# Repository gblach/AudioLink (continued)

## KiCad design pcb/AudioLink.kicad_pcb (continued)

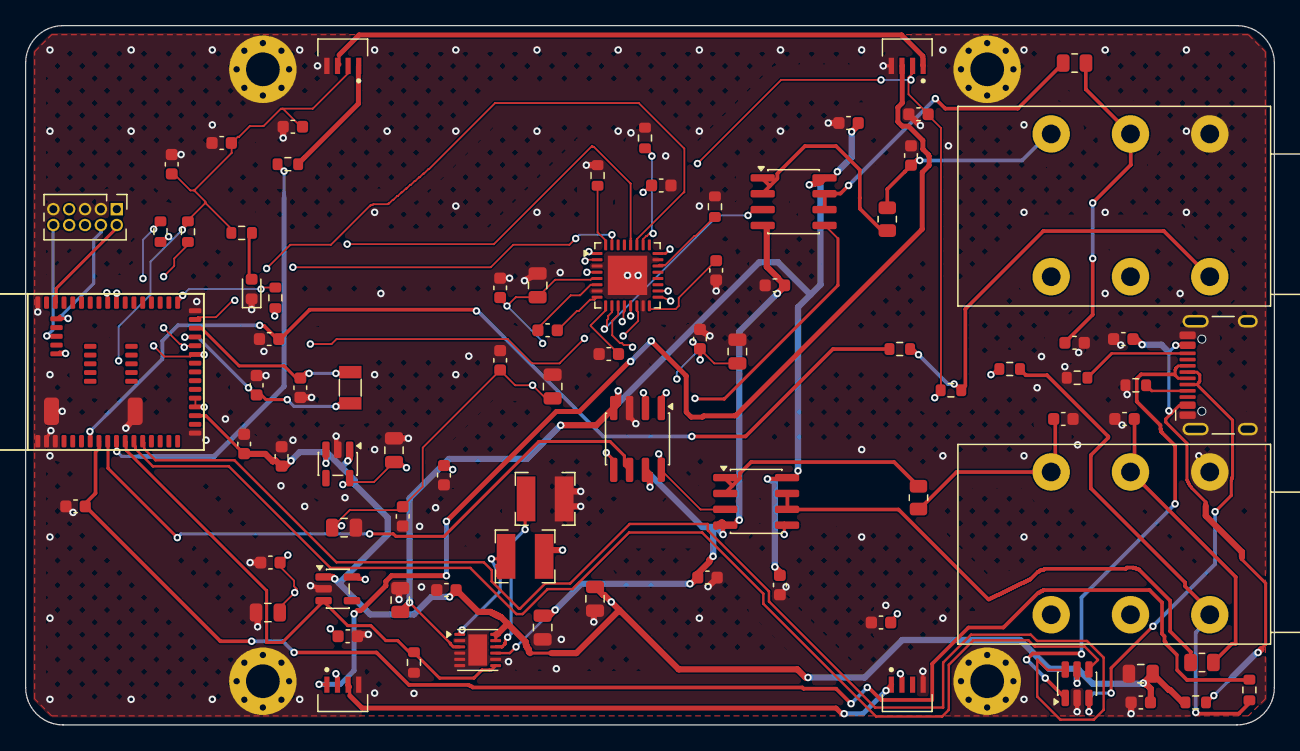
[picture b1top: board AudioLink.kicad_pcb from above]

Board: 4 copper layers, 100.0 x 56.0 mm, 88 parts (0 on the bottom side), 60 nets.

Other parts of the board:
H1, H2, H3, H4: MountingHole_2.7mm_M2.5_Pad_Via_0p5

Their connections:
GND: H1.1, H2.1, H3.1, H4.1; also elsewhere on the board

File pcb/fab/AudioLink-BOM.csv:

"Item","Designator","Qty","Manufacturer","MPN","Value","Footprint","Type","Notes"
"1","C1","1","","","4u7/10V/X7R","C_0805","SMD","LCSC: https://www.lcsc.com/search?q=4.7uF+0805+10V+X7R"
"2","C2,C6,C9,C11,C18-C20,C22,C24,C34-C43","19","","","100n/25V/X7R","C_0603","SMD","LCSC: https://www.lcsc.com/search?q=100nF+0603+25V+X7R"
"3","C3","1","","","10n/50V/X7R","C_0603","SMD","LCSC: https://www.lcsc.com/search?q=10nF+0603+50V+X7R"
"4","C4,C7,C17,C26,C29","5","","","1u/16V/X7R","C_0603","SMD","LCSC: https://www.lcsc.com/search?q=1uF+0603+16V+X7R"
"5","C5,C8,C21,C23,C25","5","","","10u/10V/X7R","C_0805","SMD","LCSC: https://www.lcsc.com/search?q=10uF+0805+10V+X7R"
"6","C10","1","","","22u/10V/X7R","C_0805","SMD","LCSC: https://www.lcsc.com/search?q=22uF+0805+10V+X7R"
"7","C12-C14","3","","","10u/16V/X7R","C_0805","SMD","LCSC: https://www.lcsc.com/search?q=10uF+0805+16V+X7R"
"8","C15,C16","2","","","7p/50V/C0G","C_0603","SMD","LCSC: https://www.lcsc.com/search?q=7pF+0603+50V+C0G. C0G required - crystal load capacitor"
"9","C27,C28","2","","","2u2/16V/X7R","C_0603","SMD","LCSC: https://www.lcsc.com/search?q=2.2uF+0603+16V+X7R"
"10","C30-C33","4","","","100p/50V/C0G","C_0603","SMD","LCSC: https://www.lcsc.com/search?q=100pF+0603+50V+C0G. C0G required - audio output EMI shunt"
"11","D1-D4","4","Worldsemi","WS2812B-4020-V6","WS2812B-4020-V6","LED_WS2812B-4020","SMD","LCSC C52941387 - https://www.lcsc.com/search?q=C52941387"
"12","D5","1","Gui guang light","GL0603UB01","Blue","LED_0603","SMD","LCSC C51933294 - https://www.lcsc.com/search?q=C51933294. Low-Vf blue, 2.6-2.9V - needed because R19 leaves only 0.4-0.7V across it from the 3V3 rail"
"13","D6","1","STMicroelectronics","USBLC6-2SC6","USBLC6-2SC6","SOT-23-6","SMD","LCSC C7519 - https://www.lcsc.com/search?q=C7519. Genuine ST. Cheaper UMW equivalent C2687116 - https://www.lcsc.com/search?q=C2687116"
"14","FB1","1","Murata","BLM18PG221SN1D","220R@100MHz","R_0603","SMD","LCSC C80165 - https://www.lcsc.com/search?q=C80165"
"15","L1,L2","2","Sunlord","SWPA4020S4R7MT","4u7/1.34A","L_Bourns-SRN4018","SMD","LCSC C48427 - https://www.lcsc.com/search?q=C48427"
"16","R1,R2","2","","","5k1/1%","R_0603","SMD","LCSC: https://www.lcsc.com/search?q=5.1k+0603+1%. 1% required - USB-C CC pulldown"
"17","R3,R12,R13","3","","","100k","R_0603","SMD","LCSC: https://www.lcsc.com/search?q=100k+0603"
"18","R4,R5","2","","","4k7","R_0603","SMD","LCSC: https://www.lcsc.com/search?q=4.7k+0603"
"19","R7,R17,R18","3","","","0R","R_0603","SMD","LCSC: https://www.lcsc.com/search?q=0R+0603"
"20","R8-R11","4","","","100R/1%","R_0805","SMD","LCSC: https://www.lcsc.com/search?q=100R+0805+1%. 1% required - these set the balanced source impedance and CMRR"
"21","R14,R15","2","","","10k","R_0603","SMD","LCSC: https://www.lcsc.com/search?q=10k+0603"
"22","R16,R19","2","","","470R","R_0603","SMD","LCSC: https://www.lcsc.com/search?q=470R+0603"
"23","U1","1","MinewSemi","MS45SF1-1Y40AIR","MS45SF1","MinewSemi_MS45SF1","SMD","Digikey - https://www.digikey.com/en/products/result?keywords=MS45SF1-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 Not stocked at LCSC"
"24","U2","1","Texas Instruments","PCM5242RHBR","PCM5242","VQFN-32","SMD","LCSC C471871 - https://www.lcsc.com/search?q=C471871"
"25","U3,U4","2","Texas Instruments","OPA1678IDR","OPA1678","SOIC-8","SMD","LCSC C192421 - https://www.lcsc.com/search?q=C192421"
"26","U5","1","Vishay","DG419DY-T1-E3","DG419","SOIC-8","SMD","LCSC C6581 - https://www.lcsc.com/search?q=C6581"
"27","U6","1","Texas Instruments","TPS65133DPDR","TPS65133","WSON-12","SMD","LCSC C134100 - https://www.lcsc.com/search?q=C134100"
"28","U7,U8","2","Texas Instruments","TLV75533PDBVR","TLV75533","SOT-23-5","SMD","LCSC C404027 - https://www.lcsc.com/search?q=C404027"
"29","Y1","1","Seiko Epson","FC-135 32.7680KA-A5","32.768kHz/7pF","Crystal_SMD_3215","SMD","Digikey - https://www.digikey.com/en/products/result?keywords=FC-135+3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 LCSC equivalent: Seiko SC-32S C97604, same 3215 / 7pF / 20ppm - https://www.lcsc.com/search?q=C97604"
"30","J1,J2","2","Neutrik","NRJ6HM-1","6.35mm TRS","Jack_6.35mm_Neutrik_NRJ6HM-1_TrimCrtYd","THT","Mouser 568-NRJ6HM1 - https://www.mouser.com/c/?q=NRJ6HM-1"
"31","J3","1","SHOU HAN","TYPE-C 16PIN 2MD(073)","USB-C","USB_C_Receptacle_HCTL_HC-TYPE-C","THT","LCSC C2765186 - https://www.lcsc.com/search?q=C2765186"
"32","J4","1","Wurth Elektronik","62201021621","SWD","PinHeader_2x05_P1.27mm_Vertical","THT","Digikey - https://www.digikey.com/en/products/result?keywords=62201021621"
